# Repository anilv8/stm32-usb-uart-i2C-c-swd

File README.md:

# STM32 with USB + UART + I2C + SWD
STM32F103C8T6 with USM micro B, UART, I2C and SWD.
Dimensions: 42 mm x 30 mm
# Schematic of circuit

## ERC Result

# PCB Board
### Front Copper

### Back copper

### Silkscreen

## DRC Result

## 3D view of PCB
### Front:

### Back:

## Gerber
### Front Copper

### Back Copper

# BOM
| Ref | Qnty | Value | Cmp name | Footprint | Description | Vendor | DNP |
| ----- | ----- | ----- | ----- | ----- | ----- | ----- | ----- |
| C1 C2 C3 C4 C9 | 5 | 100n | C | Capacitor_SMD:C_0402_1005Metric | Unpolarized capacitor |  | |
| C5 | 1 | 10u | C | Capacitor_SMD:C_0603_1608Metric | Unpolarized capacitor | | |
| C6 | 1 | 10n | C | Capacitor_SMD:C_0402_1005Metric | Unpolarized capacitor | | |
| C7 C8 | 2 | 1u | C | Capacitor_SMD:C_0402_1005Metric | Unpolarized capacitor | | |
| C10 C11 | 2 | 10p | C | Capacitor_SMD:C_0402_1005Metric | Unpolarized capacitor | | |
| C12 C13 | 2 | 22u | C | Capacitor_SMD:C_0805_2012Metric | Unpolarized capacitor | | |
| D1 | 1 | RED| LED | LED_SMD:LED_0603_1608Metric | Light emitting diode | | |
| FB1 | 1 | 120R | FerriteBead | Inductor_SMD:L_0603_1608Metric | Ferrite bead | | |
| J1 | 1 | USB_B_Micro | USB_B_Micro | Connector_USB:USB_Micro-B_Wuerth_629105150521 | USB Micro Type B connector | | |
| J2 J3 J4 | 3 | Conn_01x04_Pin| Conn_01x04_Pin | Connector_PinHeader_2.54mm:PinHeader_1x04_P2.54mm_Vertical | Generic connector, single row, 01x04, script generated | | |
| R1 | 1 | 10k | R | Resistor_SMD:R_0402_1005Metric | Resistor | | |
| R2 R3 R4 R5 | 4 | 1k5 | R | Resistor_SMD:R_0402_1005Metric | Resistor | | |
| SW1 | 1 | SW_SPDT | SW_SPDT | Button_Switch_SMD:SW_SPDT_PCM12 | Switch, single pole double throw | | |
| U1 | 1 | STM32F103C8T6 | STM32F103C8Tx | Package_QFP:LQFP-48_7x7mm_P0.5mm | STMicroelectronics Arm Cortex-M3 MCU, 64KB flash, 20KB RAM, 72 MHz, 2.0-3.6V, 37 GPIO, LQFP48  | | |
| U2 | 1 | AMS1117-3.3 | AMS1117-3.3 | Package_TO_SOT_SMD:SOT-223-3_TabPin2 | 1A Low Dropout regulator, positive, 3.3V fixed output, SOT-223 | | |
| Y1 | 1 | 16MHz | Crystal_GND24 | Crystal:Crystal_SMD_3225-4Pin_3.2x2.5mm |Four pin crystal, GND on pins 2 and 4 | | |

# REFERENCES
[1]  https://www.udemy.com/course/learn-kicad-v6-and-stm32-hardware-design/

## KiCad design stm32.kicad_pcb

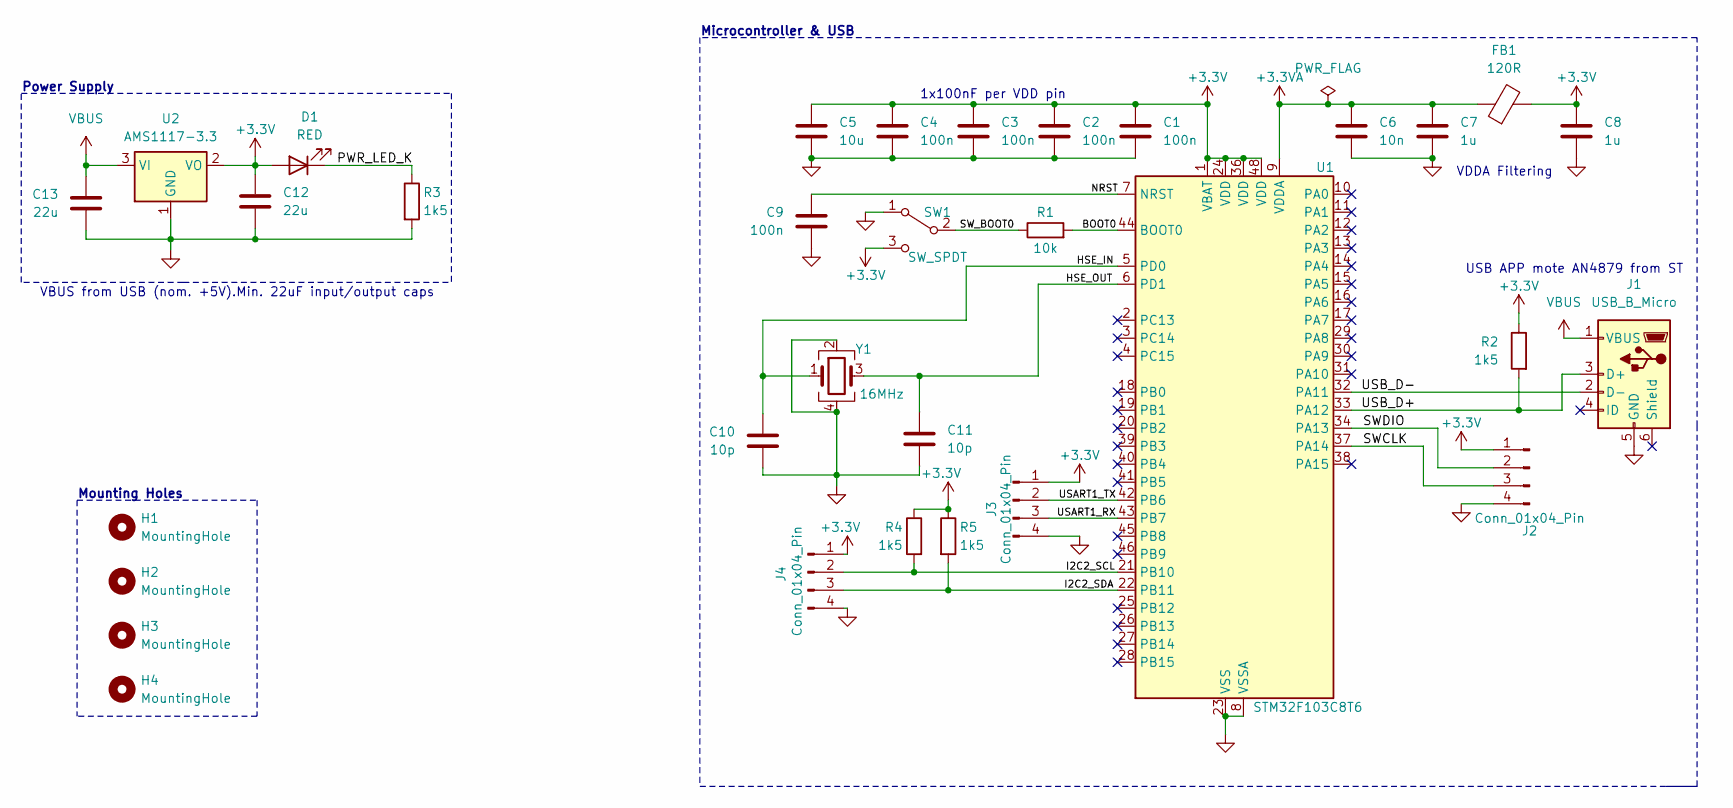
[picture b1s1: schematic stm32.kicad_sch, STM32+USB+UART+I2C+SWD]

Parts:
C1, C2, C3, C4, C9: 100n; C_0402_1005Metric
C5: 10u; C_0603_1608Metric
C6: 10n; C_0402_1005Metric
C7, C8: 1u; C_0402_1005Metric
C10, C11: 10p; C_0402_1005Metric
C12, C13: 22u; C_0805_2012Metric
D1: RED; LED_0603_1608Metric
FB1: 120R; L_0603_1608Metric
H1, H2, H3, H4: MountingHole; MountingHole_2.2mm_M2
J1: USB_B_Micro; USB_Micro-B_Wuerth_629105150521
J2, J3, J4: Conn_01x04_Pin; PinHeader_1x04_P2.54mm_Vertical
R1: 10k; R_0402_1005Metric
R2, R3, R4, R5: 1k5; R_0402_1005Metric
SW1: SW_SPDT; SW_SPDT_PCM12
U1: STM32F103C8T6; LQFP-48_7x7mm_P0.5mm
U2: AMS1117-3.3; SOT-223-3_TabPin2
Y1: 16MHz; Crystal_SMD_3225-4Pin_3.2x2.5mm

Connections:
+3.3V: C1.1, C2.1, C3.1, C4.1, C5.1, C8.1, C12.1, D1.2 (A), FB1.2, J2.1, J3.1, J4.1, R2.1, R4.1, R5.1, SW1.3 (C), U1.1 (VBAT), U1.24 (VDD), U1.36 (VDD), U1.48 (VDD), U2.2 (VO)
+3.3VA: C6.1, C7.1, FB1.1, U1.9 (VDDA)
/BOOT0: R1.2, U1.44 (BOOT0)
/HSE_IN: C10.1, U1.5 (PD0), Y1.1
/HSE_OUT: C11.1, U1.6 (PD1), Y1.3
/I2C2_SCL: J4.2, R4.2, U1.21 (PB10)
/I2C2_SDA: J4.3, R5.2, U1.22 (PB11)
/NRST: C9.1, U1.7 (NRST)
/PWR_LED_K: D1.1 (K), R3.1
/SWCLK: J2.3, U1.37 (PA14)
/SWDIO: J2.2, U1.34 (PA13)
/SW_BOOT0: R1.1, SW1.2 (B)
/USART1_RX: J3.3, U1.43 (PB7)
/USART1_TX: J3.2, U1.42 (PB6)
/USB_D+: J1.3 (D+), R2.2, U1.33 (PA12)
/USB_D-: J1.2 (D-), U1.32 (PA11)
GND: C1.2, C2.2, C3.2, C4.2, C5.2, C6.2, C7.2, C8.2, C9.2, C10.2, C11.2, C12.2, C13.2, J1.5 (GND), J2.4, J3.4, J4.4, R3.2, SW1.1 (A), U1.8 (VSSA), U1.23 (VSS), U1.35 (VSS), U1.47 (VSS), U2.1 (GND), Y1.2, Y1.4
VBUS: C13.1, J1.1 (VBUS), U2.3 (VI)

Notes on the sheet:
Power Supply
Microcontroller & USB
VBUS from USB (nom. +5V).Min. 22uF input/output caps
VDDA Filtering
1x100nF per VDD pin
USB APP mote AN4879 from ST
Mounting Holes

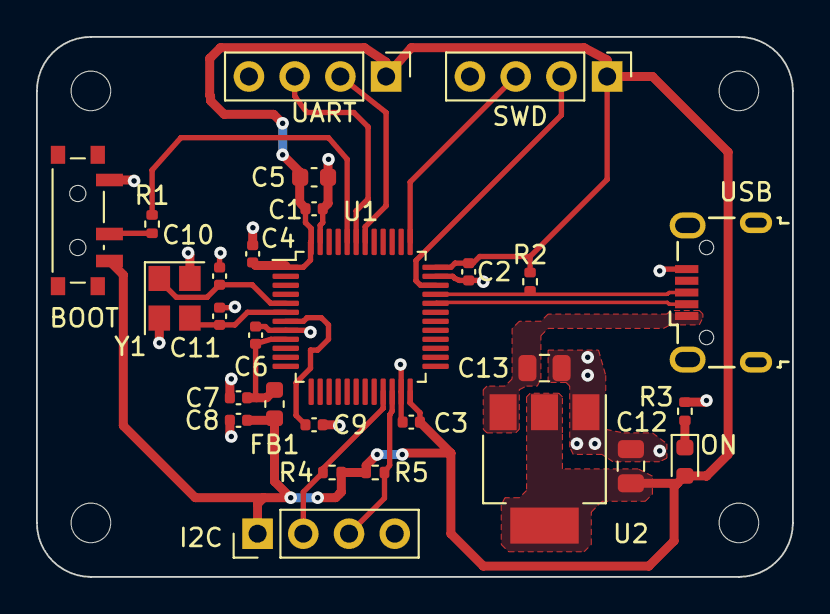
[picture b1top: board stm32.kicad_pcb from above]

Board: 2 copper layers, 42.0 x 30.0 mm, 32 parts (0 on the bottom side), 18 nets.
